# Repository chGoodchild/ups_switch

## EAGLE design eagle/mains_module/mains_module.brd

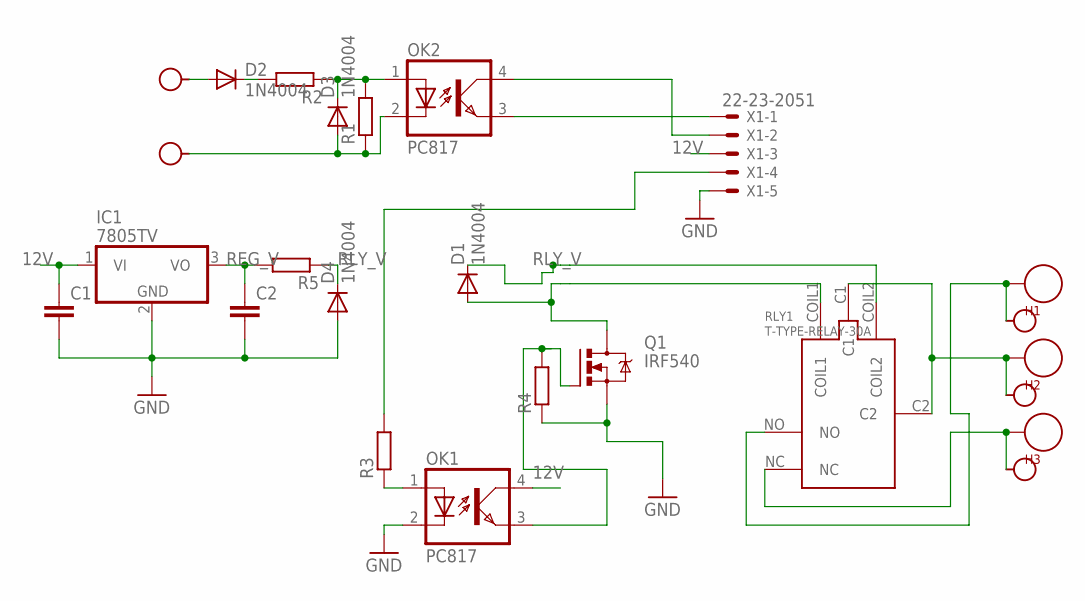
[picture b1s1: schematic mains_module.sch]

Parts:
C1, C2: C2,5-3; C2.5-3
D1, D2, D3, D4: 1N4004; DO41-10
H1, H2, H3: SEW_HOLE; SIMPLE_HOLE
H4, H5, H6, H7, H8: SEW_HOLE-SMALL; SIMPLE_HOLE_SM
IC1: 7805TV; TO220V
OK1, OK2: PC817; DIL04
Q1: IRF540; TO220BV
R1, R2, R3, R4, R5: R-EU_0207/7; 0207/7
RLY1: T-TYPE-RELAY-30A
X1: 22-23-2051

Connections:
12V: C1.1, IC1.1 (VI), OK1.4 (COL), X1.3
GND: C1.2, C2.2, D4.A, IC1.2 (GND), OK1.2 (C), Q1.S, R4.1, X1.5
unnamed: OK2.3 (EMIT), X1.1
unnamed: OK2.4 (COL), X1.2
unnamed: H1.P$1, H4.P$1, RLY1.NO
unnamed: OK1.1 (A), R3.1
unnamed: D1.A, Q1.D, RLY1.COIL1
unnamed: R3.2, X1.4
unnamed: OK1.3 (EMIT), Q1.G, R4.2
unnamed: D2.C, R2.2
unnamed: H3.P$1, H6.P$1, RLY1.NC
unnamed: D2.A, H8.P$1
unnamed: D3.C, OK2.1 (A), R1.2, R2.1
unnamed: D3.A, H7.P$1, OK2.2 (C), R1.1
unnamed: H2.P$1, H5.P$1, RLY1.C1, RLY1.C2
REG_V: C2.1, IC1.3 (VO), R5.2
RLY_V: D1.C, D4.C, R5.1, RLY1.COIL2

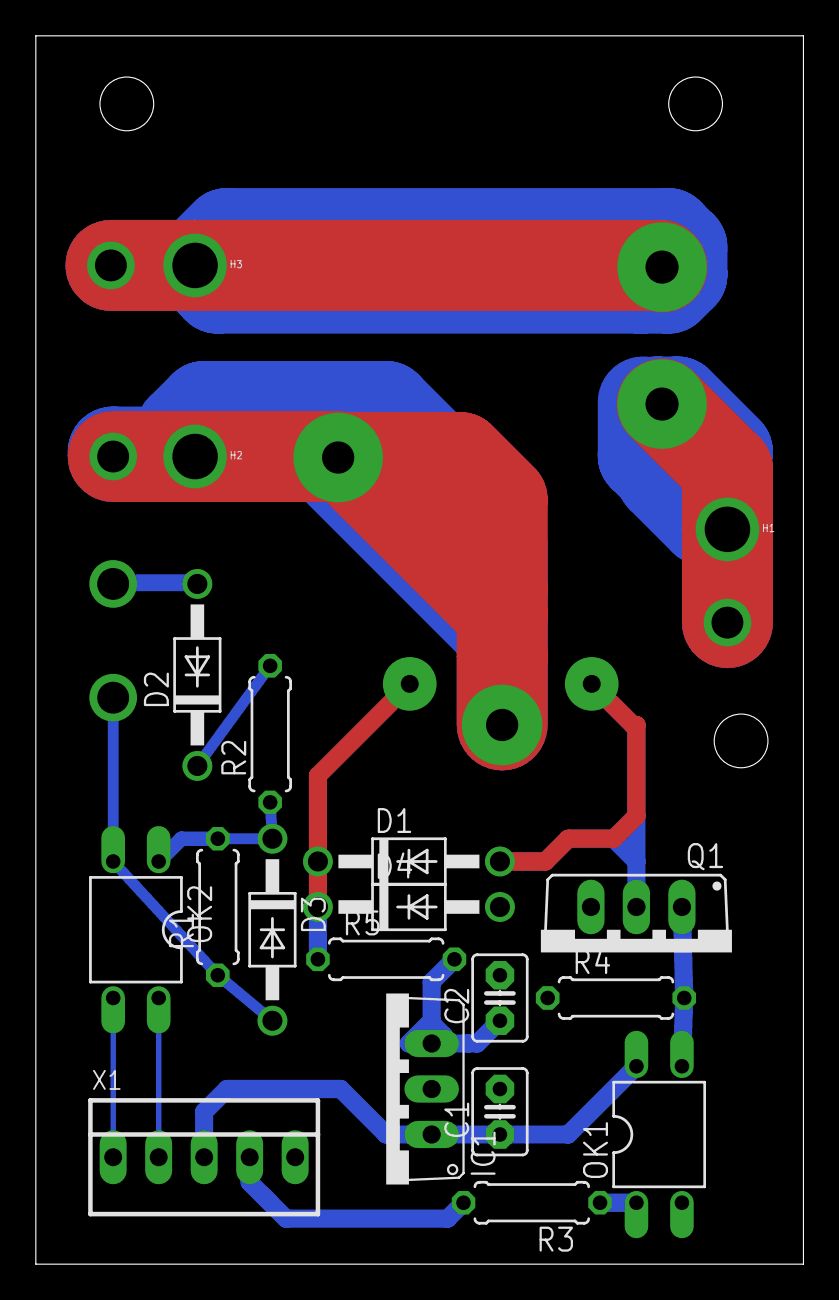
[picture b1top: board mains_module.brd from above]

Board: 2 copper layers, 42.9 x 68.6 mm, 25 parts (0 on the bottom side), 17 nets.

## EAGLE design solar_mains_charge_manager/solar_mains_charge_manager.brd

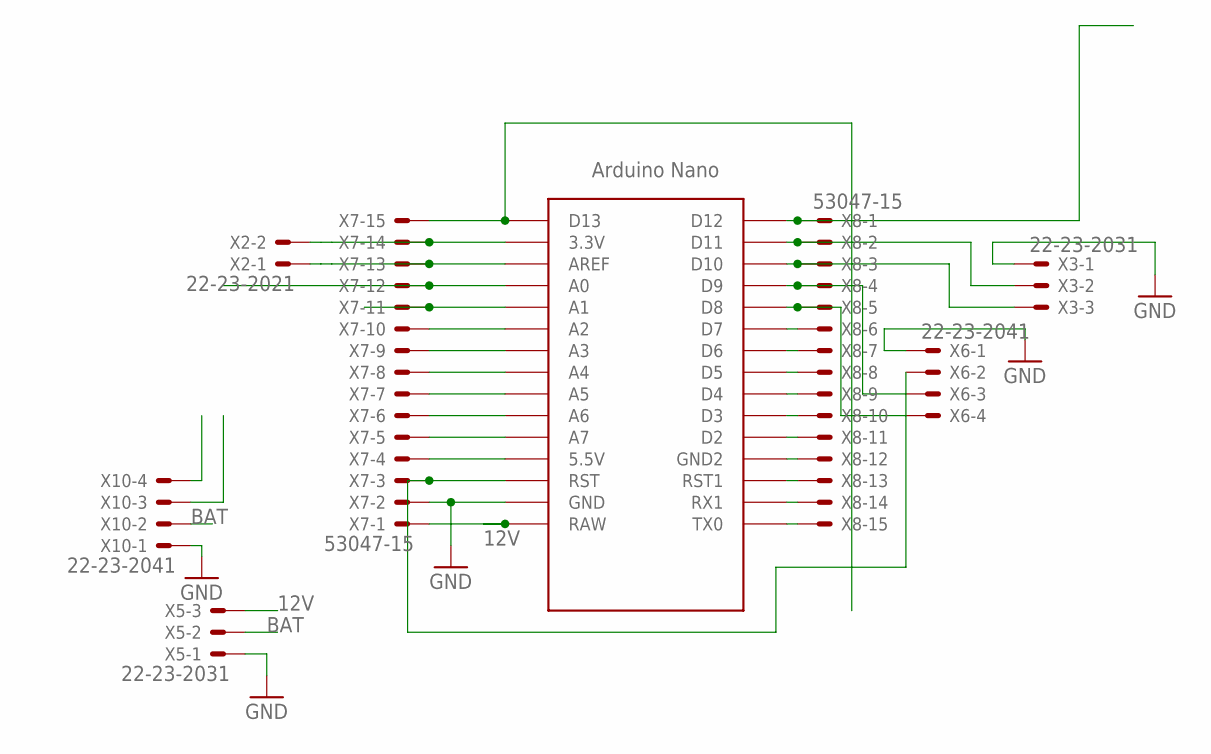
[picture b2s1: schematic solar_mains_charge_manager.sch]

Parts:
U$1: NANO
X2: 22-23-2021
X3, X5: 22-23-2031
X6, X10: 22-23-2041
X7, X8: 53047-15

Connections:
12V: U$1.RAW, X5.3, X7.1
12V1: U$1.AREF, X2.1, X7.13
BAT: X5.2, X10.2
GND: U$1.GND, X3.1, X5.1, X6.1, X7.2, X10.1
unnamed: U$1.D13, X7.15
unnamed: U$1.3.3V, X2.2, X7.14
unnamed: U$1.D12, X8.1
unnamed: U$1.D11, X3.2, X8.2
unnamed: U$1.D10, X3.3, X8.3
unnamed: U$1.D9, X6.3, X8.4
unnamed: U$1.D8, X6.4, X8.5
unnamed: U$1.RST, X6.2, X7.3
unnamed: U$1.D7, X8.6
unnamed: U$1.D6, X8.7
unnamed: U$1.D5, X8.8
unnamed: U$1.D4, X8.9
unnamed: U$1.D3, X8.10
unnamed: U$1.D2, X8.11
unnamed: U$1.GND1 (GND2), X8.12
unnamed: U$1.RST1, X8.13
unnamed: U$1.RX1, X8.14
unnamed: U$1.TX0, X8.15
unnamed: U$1.5V (5.5V), X7.4
unnamed: U$1.A7, X7.5
unnamed: U$1.A6, X7.6
unnamed: U$1.A5, X7.7
unnamed: U$1.A4, X7.8
unnamed: U$1.A3, X7.9
unnamed: U$1.A2, X7.10
unnamed: U$1.A1, X7.11
unnamed: U$1.A0, X7.12

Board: 2 copper layers, 8 parts (0 on the bottom side), 31 nets, no tracks yet.

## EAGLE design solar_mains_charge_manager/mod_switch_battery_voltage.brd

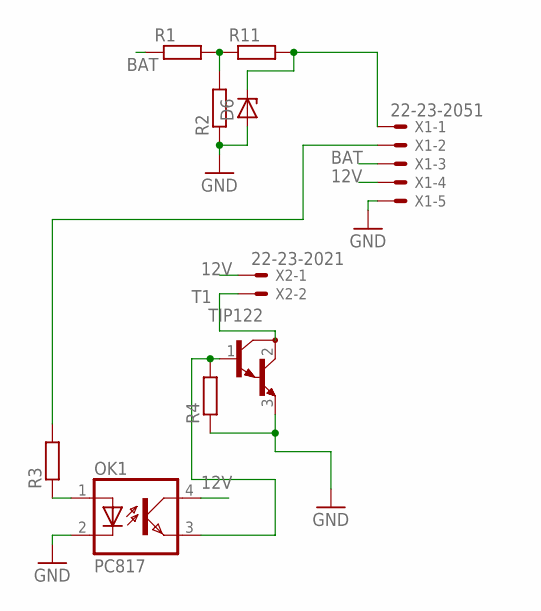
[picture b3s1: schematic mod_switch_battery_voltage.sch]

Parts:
D6: ZENER-DIODEDO34-7; DO34Z7
OK1: PC817; DIL04
R1, R2, R3, R4, R11: R-EU_0204/5; 0204/5
T1: TIP122; TO220
X1: 22-23-2051
X2: 22-23-2021

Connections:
12V: OK1.4 (COL), X1.4, X2.1
BAT: R1.1, X1.3
GND: D6.A, OK1.2 (C), R2.1, R4.1, T1.3 (E), X1.5
unnamed: OK1.1 (A), R3.1
unnamed: T1.2 (C), X2.2
unnamed: R3.2, X1.2
unnamed: OK1.3 (EMIT), R4.2, T1.1 (B)
unnamed: D6.C, R11.2, X1.1
unnamed: R1.2, R2.2, R11.1

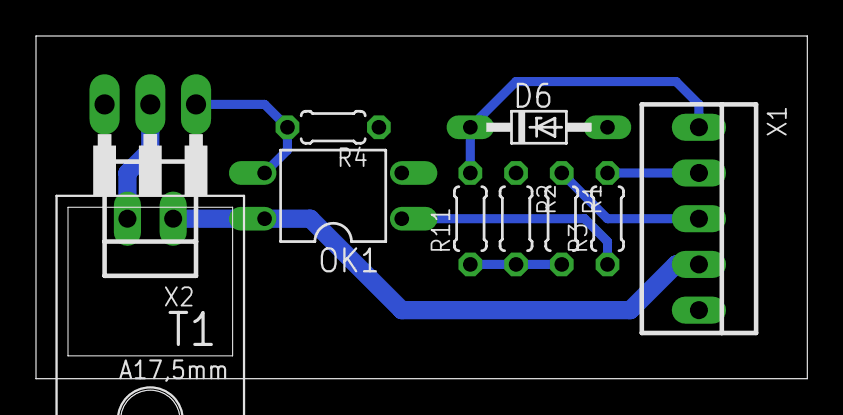
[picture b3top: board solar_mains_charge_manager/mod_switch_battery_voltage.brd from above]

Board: 2 copper layers, 42.9 x 19.0 mm, 10 parts (0 on the bottom side), 9 nets.

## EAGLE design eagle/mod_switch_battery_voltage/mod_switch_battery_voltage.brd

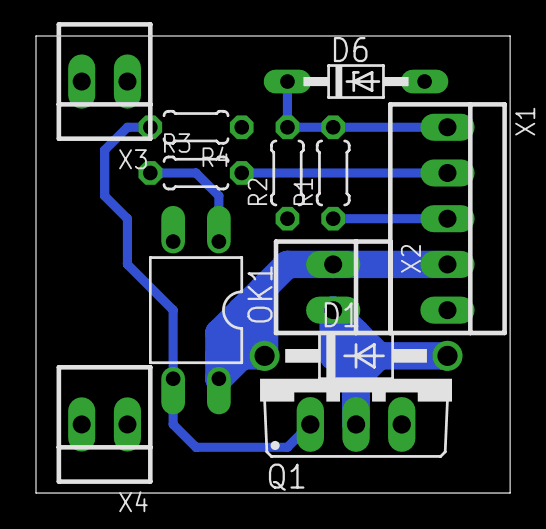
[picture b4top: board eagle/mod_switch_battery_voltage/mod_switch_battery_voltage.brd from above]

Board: 2 copper layers, 26.3 x 25.4 mm, 12 parts (0 on the bottom side), 8 nets.

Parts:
D1: 1N4004; DO41-10
D6: DO34Z7
OK1: PC817; DIL04
Q1: IRF540; TO220BV
R1, R2, R3, R4: 0204/5
X1: 22-23-2051
X2, X3, X4: 22-23-2021

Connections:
12V: D1.C, OK1.4, X1.4, X2.1
BAT: R1.1, X1.3
GND: D6.A, OK1.2, Q1.S, R2.1, R4.1, X1.5, X3.1, X3.2, X4.1, X4.2
unnamed: OK1.1, R3.1
unnamed: D1.A, Q1.D, X2.2
unnamed: R3.2, X1.2
unnamed: OK1.3, Q1.G, R4.2
unnamed: D6.C, R1.2, R2.2, X1.1

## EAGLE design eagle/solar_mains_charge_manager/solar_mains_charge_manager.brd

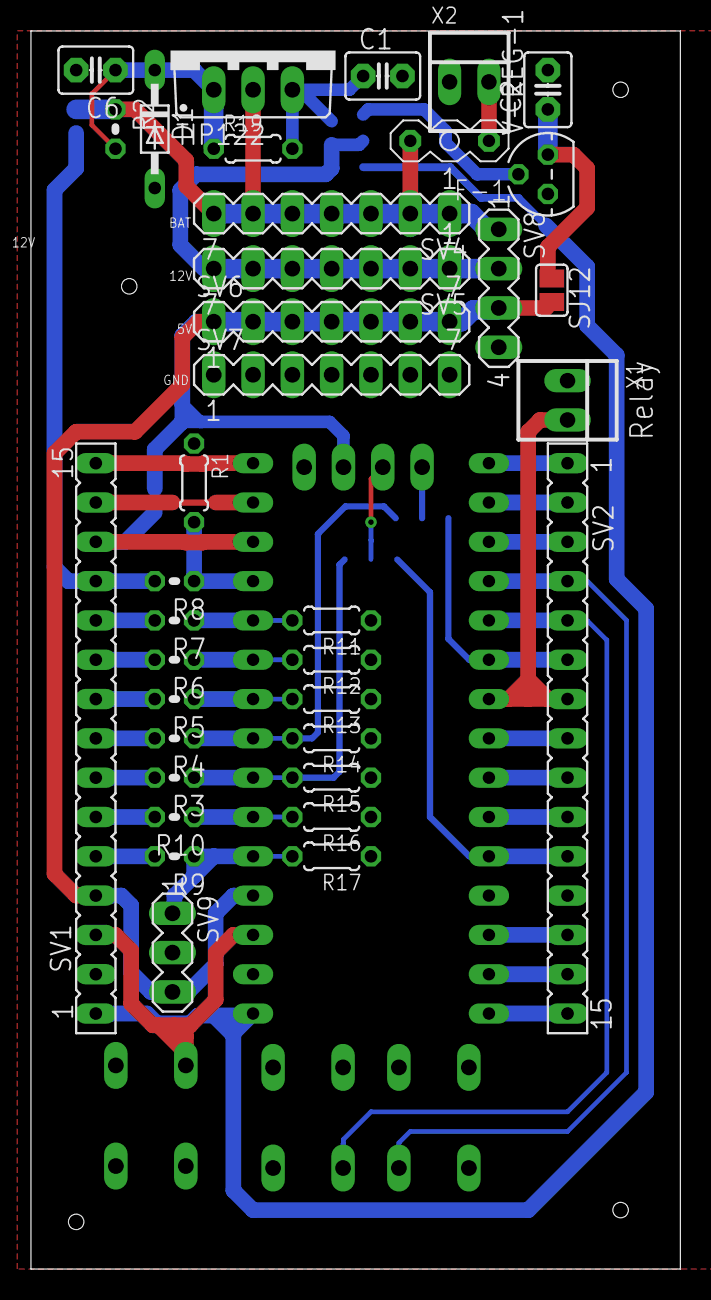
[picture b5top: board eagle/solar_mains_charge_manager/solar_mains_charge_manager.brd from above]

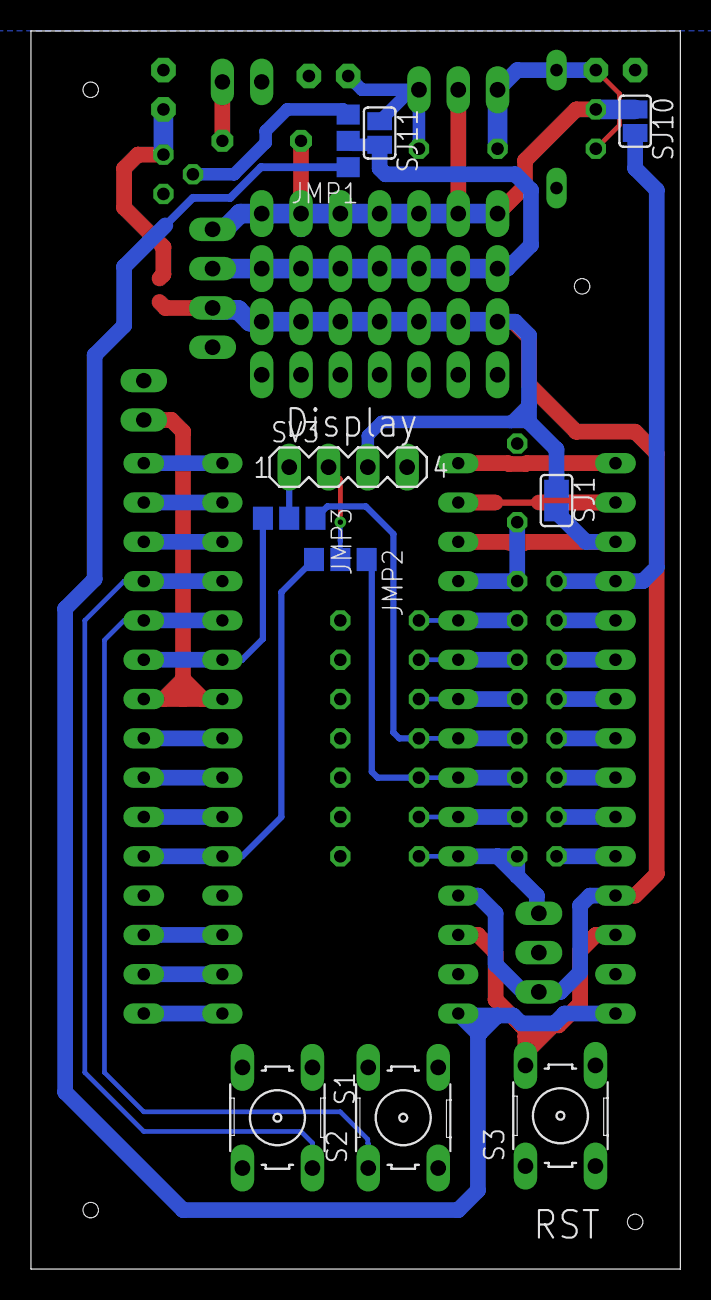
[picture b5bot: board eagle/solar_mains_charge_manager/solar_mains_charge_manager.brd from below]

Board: 2 copper layers, 42.0 x 80.0 mm, 47 parts (10 on the bottom side), 46 nets.

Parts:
C1, C2, C6: C2.5-3
D1: DO34Z7
F-1: FUSE
JMP1, JMP2, JMP3: 0R-JUMPA; A0R-JMP
R1, R11, R12, R13, R14, R15, R16, R17, R19: 0204/5
R2, R3, R4, R5, R6, R7, R8, R9, R10: 0204V
S1, S2, S3: B3F-10XX
SJ1, SJ10, SJ11, SJ12: SJ
SV1, SV2: FE15
SV3, SV8: MA04-1
SV4, SV5, SV6, SV7: MA07-1
SV9: MA03-1
TIP122: IRF530; TO220BV
U$1: NANO
V-REG-1: TO92
X1, X2: 22-23-2021

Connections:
5V: SJ1.1, SJ12.2, SV1.4, SV3.3, SV6.1, SV6.2, SV6.3, SV6.4, SV6.5, SV6.6, SV6.7, SV8.3, SV9.3, U$1.5V
A0: R1.2, R8.1, U$1.A0
A1: R7.1, R11.2, U$1.A1
A2: R6.1, R12.2, U$1.A2
A3: R5.1, R13.2, U$1.A3
A4: JMP3.1, R4.1, R14.2, U$1.A4
A5: JMP2.1, R3.1, R15.2, U$1.A5
A6: R10.1, R16.2, U$1.A6
A7: R9.1, R17.2, SV9.1, U$1.A7
AREF: SJ1.2, SV1.13, U$1.AREF
BAT: F-1.P$2, R2.1, SJ10.1, SV4.1, SV4.2, SV4.3, SV4.4, SV4.5, SV4.6, SV4.7, SV8.1, TIP122.D
D8: S2.1, SV2.5, U$1.D8
D9: S1.2, SV2.4, U$1.D9
GND: C1.2, C2.2, C6.2, D1.A, R1.1, R11.1, R12.1, R13.1, R14.1, R15.1, R16.1, R17.1, S1.4, S2.4, S3.4, SV1.2, SV2.12, SV3.4, SV7.1, SV7.2, SV7.3, SV7.4, SV7.5, SV7.6, SV7.7, SV8.4, SV9.2, U$1.GND, U$1.GND1, V-REG-1.1, X1.1, X2.1
unnamed: C1.1, R19.2, SJ11.1, TIP122.S
unnamed: SV1.15, U$1.D13
unnamed: C6.1, D1.C, R2.2, R19.1, TIP122.G
unnamed: SV2.1, U$1.D12
unnamed: SV1.14, U$1.3.3V
unnamed: JMP1.3, V-REG-1.2
unnamed: SV2.2, U$1.D11
unnamed: F-1.P$1, X2.2
unnamed: JMP2.2, SV3.2
unnamed: JMP3.2, SV3.1
unnamed: SV2.3, U$1.D10
unnamed: C2.1, SJ12.1, V-REG-1.3
unnamed: JMP1.2, SJ11.2, SV5.1, SV5.2, SV5.3, SV5.4, SV5.5, SV5.6, SV5.7, SV8.2
unnamed: SV2.8, U$1.D5
unnamed: SV2.9, U$1.D4
unnamed: SV2.10, U$1.D3
unnamed: SV2.13, U$1.RST1
unnamed: SV2.14, U$1.RX1
unnamed: SV2.15, U$1.TX0
RELAY: SV2.7, U$1.D6, X1.2
RST: S3.2, SV1.3, U$1.RST
SCLSW: JMP2.3, SV2.11, U$1.D2
SDASW: JMP3.3, SV2.6, U$1.D7
VD0: R8.2, SJ10.2, SV1.12
VD1: R7.2, SV1.11
VD2: R6.2, SV1.10
VD3: R5.2, SV1.9
VD4: R4.2, SV1.8
VD5: R3.2, SV1.7
VD6: R10.2, SV1.6
VD7: R9.2, SV1.5
VIN: JMP1.1, SV1.1, U$1.RAW

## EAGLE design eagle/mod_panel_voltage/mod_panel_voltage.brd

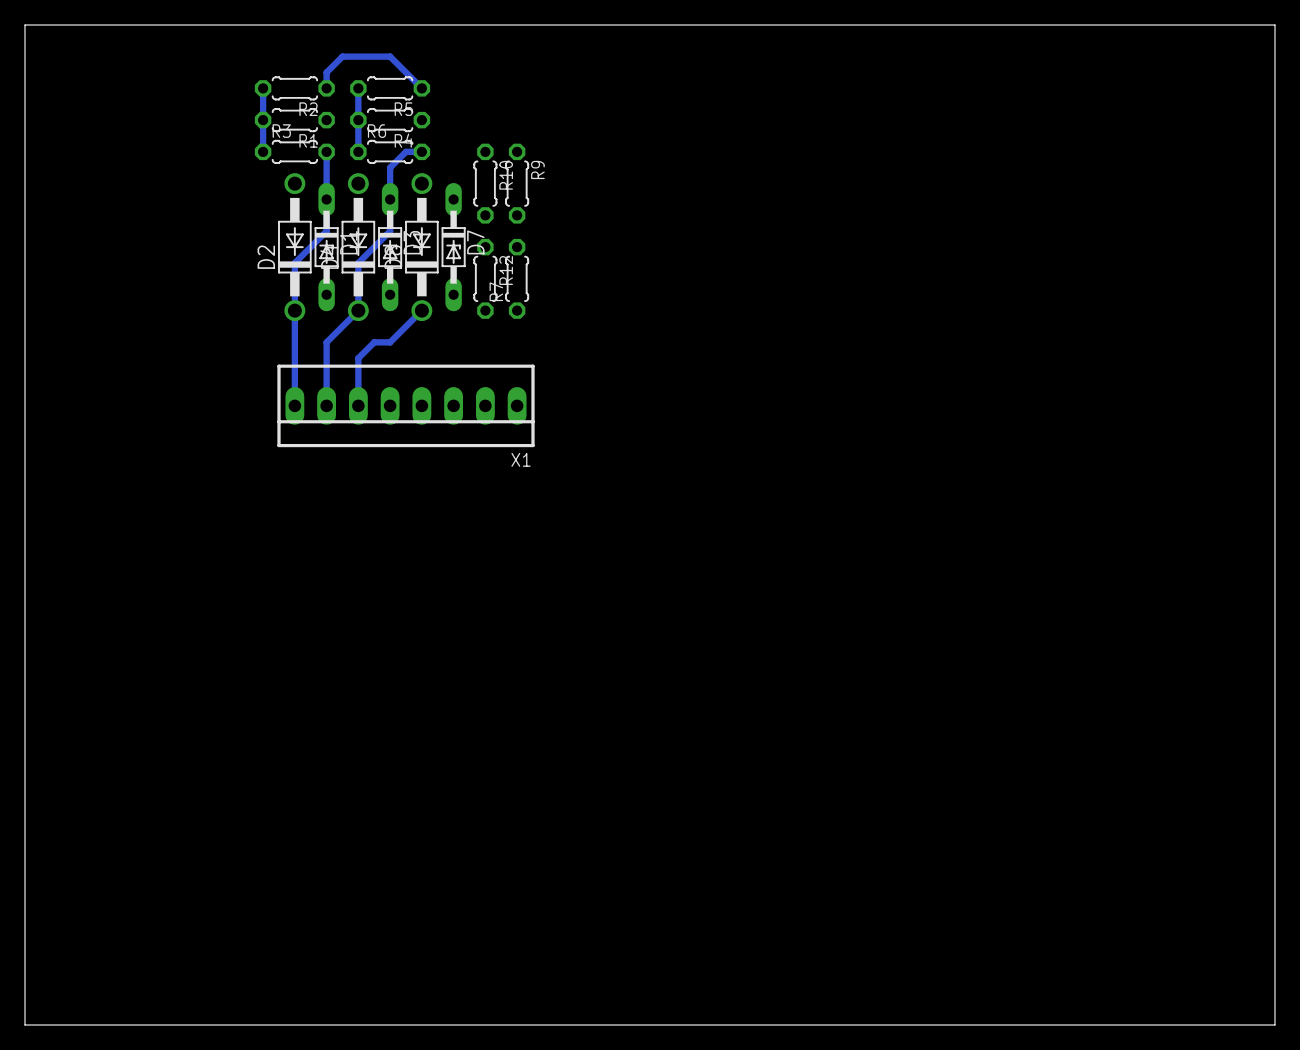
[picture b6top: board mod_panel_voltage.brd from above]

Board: 2 copper layers, 100.0 x 80.0 mm, 17 parts (0 on the bottom side), 10 nets.

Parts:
D1, D3, D7: DO34Z7
D2, D4, D8: 1N4004; DO41-10
R1, R2, R3, R4, R5, R6, R7, R9, R10, R12: 0204/5
X1: 22-23-2081

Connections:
ADC1: D3.C, D4.C, R6.2, X1.7
ADC2: D1.C, D2.C, R3.2, X1.8
ADC3: D7.C, D8.C, R12.2, X1.6
GND: D1.A, D2.A, D3.A, D4.A, D7.A, D8.A, R1.1, R9.1, X1.1, X1.4
unnamed: R7.2, R9.2, R10.2, R12.1
unnamed: R1.2, R2.2, R3.1
unnamed: R4.2, R5.2, R6.1
P+: R2.1, R5.1, X1.3
P-: R4.1, R10.1, X1.2
VCOMP: R7.1, X1.5

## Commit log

2017-11-25 After working with Dyuman. I have to ask him for the code...
2018-01-10 Added stuff, it's still a mess, will re-organize
2018-01-10 Some more schematic and spreadsheet
2018-01-10 Deleted corrupted eagle schematic file. After having opened psu_considerations.ods in LibreOffice, git detects as if there were changes in it (actually there weren't)
2018-01-11 Updated calculation solar panel plot in psu_considerations.ods
2018-01-11 psu_considerations: added functions to easily switch between plots for different system voltages and conditional formatting to highlight voltages out of bounds
2018-01-11 Added solar panel voltage measurement along with over voltage and negative voltage protection in schematic, plus comments on the same in psu_considerations.ods
2018-01-11 Continued work on adding overvoltage protection on analog inputs and measurement of solar panel voltage
2018-01-12 Continued work on solar panel voltage measurement, added code to read analog input and calculate voltage, with hard-coded (for now) battery voltage and temporarily reading A0
2018-01-14 psu_considerations.ods: started preparing list of definable settings for program
2018-01-16 Added panel_measurement1.xml
2018-01-16 psu_considerations.ods: worked on panel voltage plot
2018-01-22 A lot of stuff
2018-01-26 Finished board layout of mod_switch_battery_voltage and more work on psu_considerations.ods
2018-01-27 psu_considerations.ods: added possible modules list sheet
2018-02-02 psu_considerations.ods: misc. notes
2018-02-03 psu_considerations.ods: misc. updates. Fixed code to switch on and off at 23.4 / 26, and print relay status on USB
2018-02-07 Input impedance is negligible...
2018-02-07 Percentage charge of the battery
    We should soon find a function that describes the batteries behavior in order to better understand it...
    https://scubaengineer.com/dndocuments/lead_acid_battery_charging_graphs.pdf
2018-02-09 Large due to voltage offset.
2018-02-09 We still have an offset. Maybe the sensor isn't providing enough current?
2018-03-03 Added a function for checking the battery state, but it has not been tested yet...
2018-03-03 Stuff
2018-03-03 Corrected currents and charge time
2018-03-05 My first attempt ant limiting the range of the functions. A lot of potential problems were fixed...
2018-03-14 Tested the function with scaling and it seems to be working, but I need a moving average because of the crazy input from the battery charger...
2018-03-16 Working with average percentage. Let's see with real batteries...
2018-03-18 Display values on display home screen
2018-03-18 Just before testing on the Grace solar pannels...
2018-03-18 With MCP1702 voltage refference
2018-03-18 Worked on menu
2018-03-19 Misc. small changes
2018-03-22 Added relay purchase advance in expense list
2018-03-22 Started work on mains_module
2018-03-23 Worked on relay and updated expences
2018-03-24 Completed T-type-relay eagle part, created schematic and board of mains_module, and updates to shopping list/expense list
2018-04-21 Tidied up and renamed the battery percentage function / folder
2018-04-21 Cleanup 1
2018-04-21 removed octave things
2018-04-21 Cleanup 2
2018-04-21 added an archive
2018-04-21 minor shifting
2018-04-21 Cleanup 3
2018-04-21 board improvements
2018-04-21 Cleanup 4
2018-04-21 Cleanup 5
2018-04-21 renaming code
2018-04-21 Cleanup 6
2018-04-29 Discussed how to proceed with the code
2018-05-12 Added scan
2018-05-12 Updated the flowchart and discussed issues in a meeting
2018-05-21 Updated expenses with Last School donation
2018-05-21 Added an FS transfer of 860 rs.
2018-06-03 Discussed how to proceed with the code and shifted the current version of the percentage function into the rough code. The arduino code in the octave folder is no longer maintained so we can now work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
2018-06-03 I added some error codes. The code still hasn't been tested, but it compiles.
2018-06-03 Modularised the code. It still hasn't been tested, but it compiles...
2018-08-02 Updated expenses
2018-11-30 Create LICENSE
2019-06-10 Added comments with Dyuman
2019-06-10 Included menu library
2019-06-11 Started update MULTIMETER class to use ADS1115 ADC module instead of Arduino inbuilt, moved menu class files to version_1.0 from rough
2019-06-13 Results of function test on battery
2019-06-14 re-enabled averaging of measured values and added more test results of percentage function
2019-06-15 More function tests and averaging and ovf fixes hopefully
2019-06-15 Updated bat_tests
2019-06-15 Started work on version_1.0, minor fixes in DSP_MENU and added init_eeprom program
2019-06-26 Some changes
2019-06-27 Improvements to display library
2022-09-28 least squares works in python, but a sigmoid is required to fit this data
2022-09-28 working sigmoid for C10
2022-09-28 C20 sigmoid kind of works
2022-09-28 The charging curves are all ready, but they are all very inaccurate. I should probably split the upper half of the points from the lower half...
